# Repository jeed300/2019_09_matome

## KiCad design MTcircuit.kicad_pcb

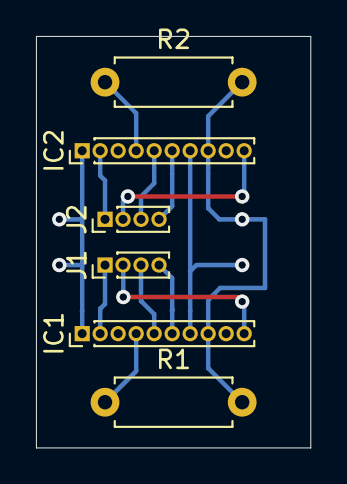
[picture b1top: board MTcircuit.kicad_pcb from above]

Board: 2 copper layers, 15.2 x 22.9 mm, 6 parts (0 on the bottom side), 12 nets.

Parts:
IC1, IC2: TA7291P(O); PinHeader_1x10_P1.00mm_Vertical
J1, J2: Conn_01x04_Female; PinHeader_1x04_P1.00mm_Vertical
R1, R2: 3kΩ; R_Axial_DIN0207_L6.3mm_D2.5mm_P7.62mm_Horizontal

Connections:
+3V3: IC1.7, IC2.7
+5V: IC1.8, IC2.8, R1.2, R2.2
GND: IC1.1, IC2.1
unnamed: IC1.2, J1.1
unnamed: IC1.4, R1.1
unnamed: IC1.6, J1.4
unnamed: IC1.5, IC1.10, J1.2, J1.3
unnamed: IC2.2, J2.1
unnamed: IC2.4, R2.1
unnamed: IC2.5, J2.3
unnamed: IC2.6, J2.4
unnamed: IC2.10, J2.2

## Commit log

2019-11-04 up
    up
2019-11-08 Add files via upload
    モータドライバの基盤データ
2019-11-10 Add Main_Screen by kitsune
    Added from RPC@PICason by kitsune
